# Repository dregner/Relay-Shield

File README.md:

# Relay-Shield
Shield for Arduino Nano with 6 relay controlled by a real time clock module

Arduino Conde Line used for turn on and turn off based on time captured from RTC and analogs systems response

--  Shield:
    Powered by a 9V DC source;
    Voltage regulator to 5V DC;
    Pin outs for analog entrance;

    Digital Signal for relays:
        Relay 1: D12;
        Relag 2: D11;
        Relay 3: D5;
        Relay 4: D4;
        Relay 5: D3;
        Relay 6: D2;

    Real Time Clock (RTC):
    Pintouts:
        DS:  A6;
        SCL: A5 (SCL for arduino);
        SDA: A4 (SDA for arduino);
  
  Analog bus of pinouts: A0, A1, A2, A3, A7;

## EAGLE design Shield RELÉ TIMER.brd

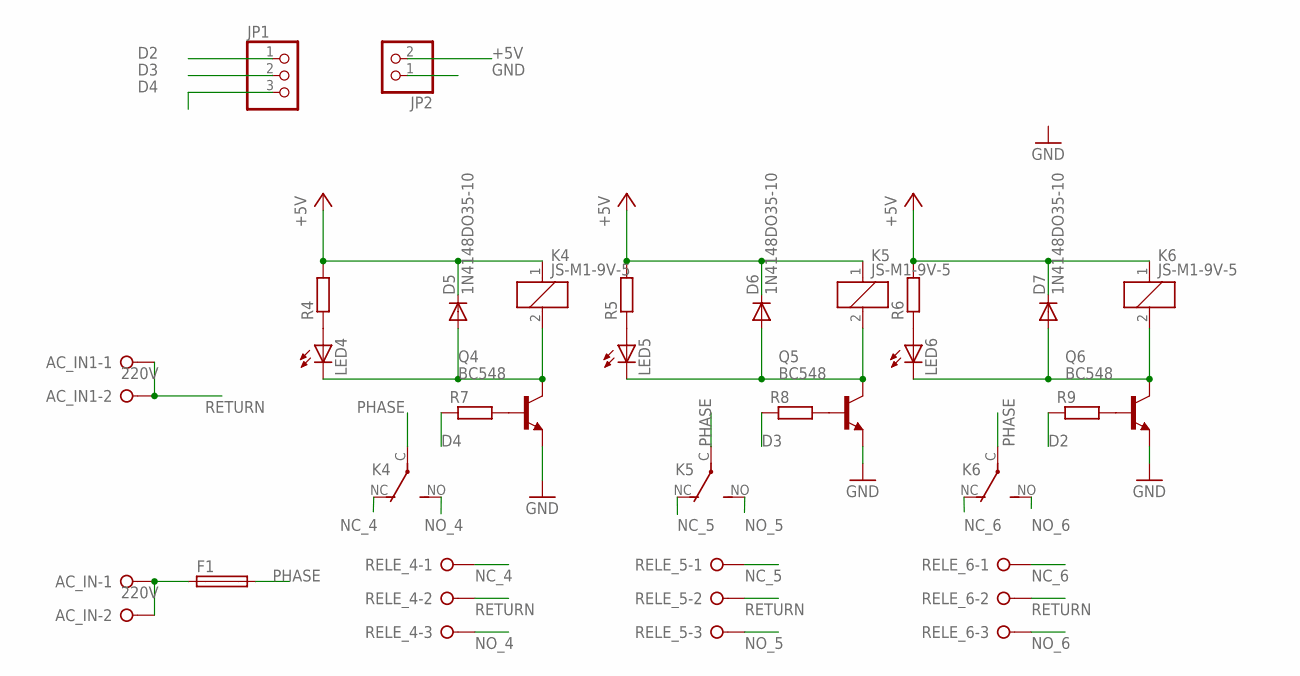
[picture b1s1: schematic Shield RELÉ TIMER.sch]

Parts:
AC_IN, AC_IN1: 220V; W237-132
D5, D6, D7: 1N4148DO35-10; DO35-10
F1: SH22,5A
JP1: PINHD-1X3; 1X03
JP2: PINHD-1X2; 1X02
K4, K5, K6: JS-M1-9V-5; JS-M
LED4, LED5, LED6: LED5MM
Q4, Q5, Q6: BC548; TO92-EBC
R4, R5, R6, R7, R8, R9: R0204/7; 0204/7
RELE_4, RELE_5, RELE_6: W237-03P; W237-133

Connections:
+5V: D5.C, D6.C, D7.C, JP2.2, K4.1, K5.1, K6.1, R4.2, R5.2, R6.2
D2: JP1.1, R9.1
D3: JP1.2, R8.1
D4: JP1.3, R7.1
GND: JP2.1, Q4.E, Q5.E, Q6.E
unnamed: LED4.A, R4.1
unnamed: LED5.A, R5.1
unnamed: LED6.A, R6.1
unnamed: D5.A, K4.2, LED4.K (C), Q4.C
unnamed: D6.A, K5.2, LED5.K (C), Q5.C
unnamed: Q4.B, R7.2
unnamed: Q5.B, R8.2
unnamed: D7.A, K6.2, LED6.K (C), Q6.C
unnamed: Q6.B, R9.2
unnamed: AC_IN.1, AC_IN.2, F1.1
NC_4: K4.NC (O), RELE_4.1
NC_5: K5.NC (O), RELE_5.1
NC_6: K6.NC (O), RELE_6.1
NO_4: K4.NO (S), RELE_4.3
NO_5: K5.NO (S), RELE_5.3
NO_6: K6.NO (S), RELE_6.3
PHASE: F1.2, K4.C, K5.C, K6.C
RETURN: AC_IN1.1, AC_IN1.2, RELE_4.2, RELE_5.2, RELE_6.2

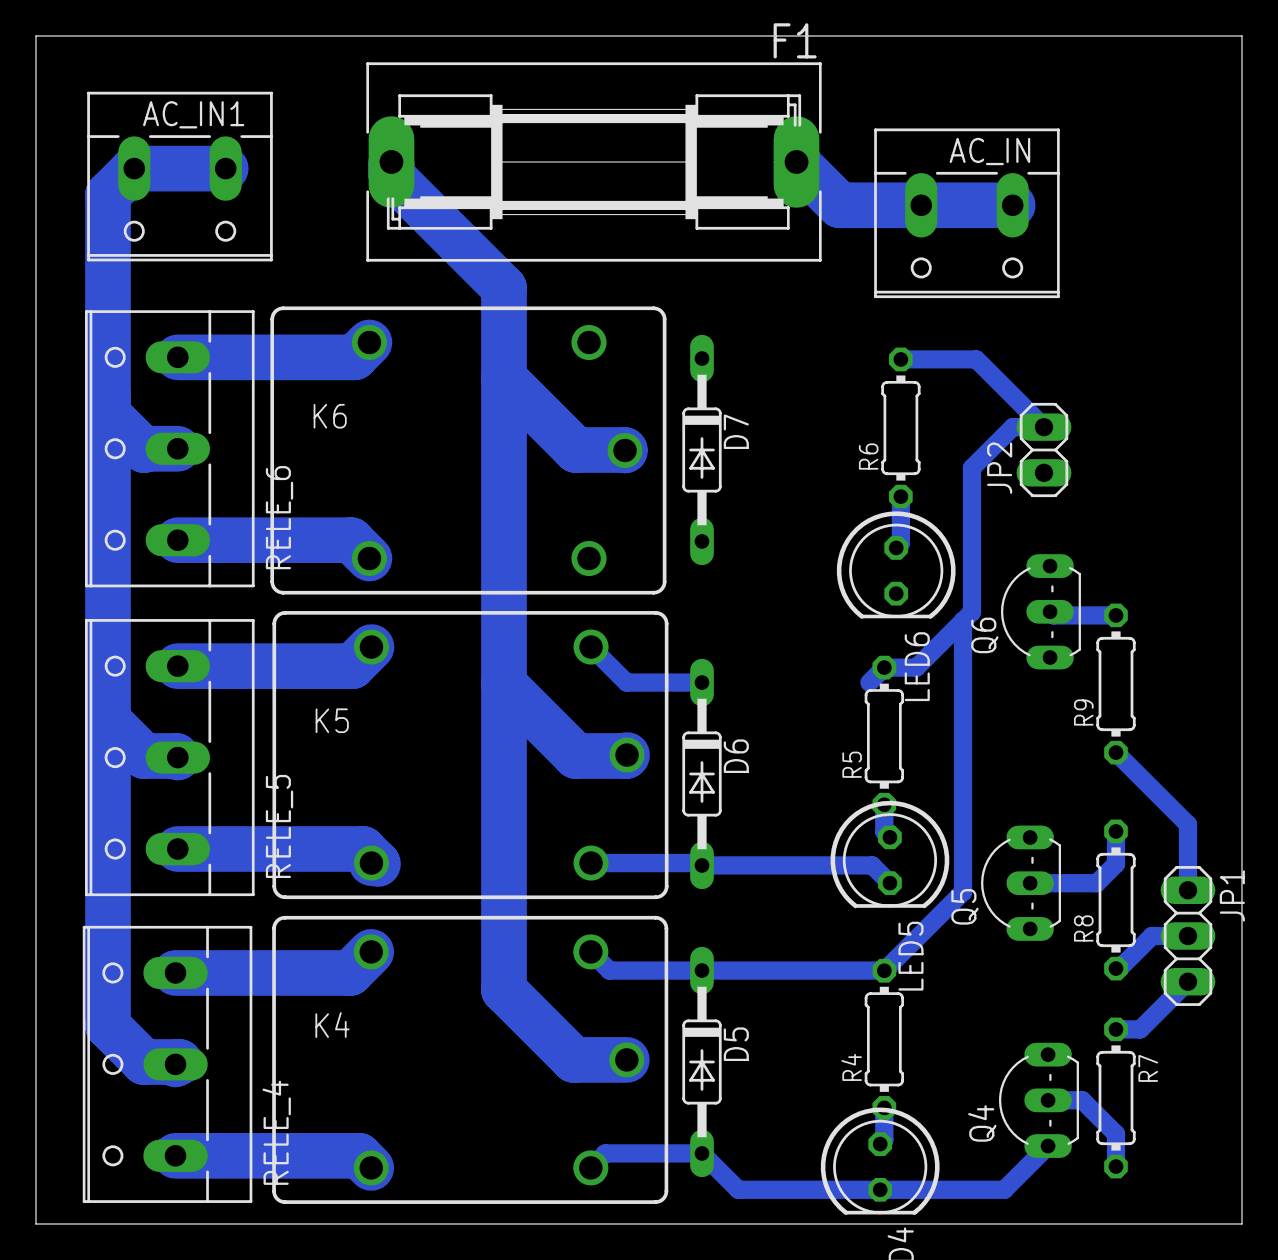
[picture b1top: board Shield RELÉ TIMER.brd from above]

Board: 2 copper layers, 67.0 x 66.0 mm, 26 parts (0 on the bottom side), 23 nets.

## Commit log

2018-02-26 Change-size
    Redução de tamanho impresso
    Mudança nas vias dos transistor para utilização de JUMPERS
    Mudança layout do regulador 7805
2018-02-28 Update README.md
    Addd descrition of arduino programm.
2018-03-01 Separete Power to Control
    Divisão das trilhas de Alta Potência das trilhas de sinal
2018-04-11 Erro de enquadro
    Corrigindo enquadro tor
2018-04-11 Transistor circuit
    Added a free wheel diode for relays bobines, resistor from arduino digital port to transistor and changing the structure of the board.
2018-09-13 Modulo
    Separação modulo com reles
2018-10-11 Relay module
    Develop three relay module
